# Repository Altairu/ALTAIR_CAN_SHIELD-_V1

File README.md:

# ALTAIR_CAN_SHIELD-_V1
ALTAIR_CAN_SHIELD _V1

注意：ファイルが破損しています．
発注ファイルはCAN_V1_1.zip

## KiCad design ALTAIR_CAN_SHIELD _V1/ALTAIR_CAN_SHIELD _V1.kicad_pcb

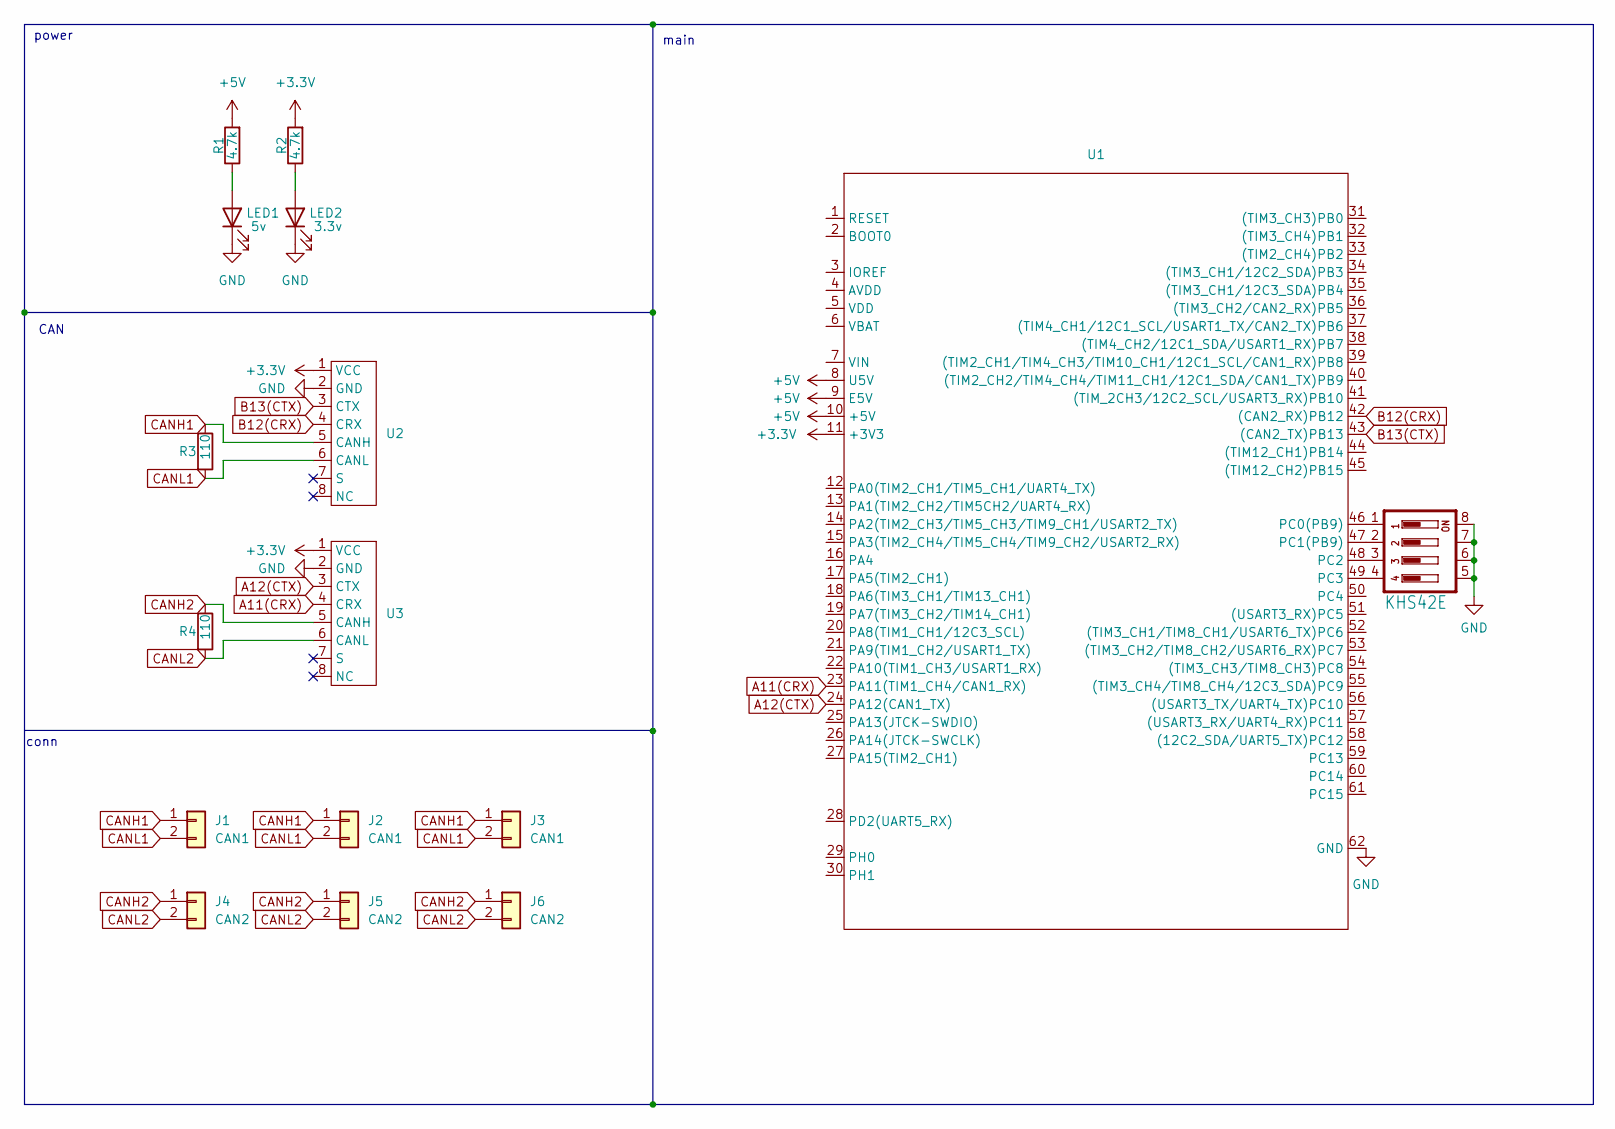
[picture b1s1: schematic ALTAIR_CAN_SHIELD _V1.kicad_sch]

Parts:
J1, J2, J3: CAN1; JST_XA_S02B-XASK-1_1x02_P2.50mm_Horizontal
J4, J5, J6: CAN2; JST_XA_S02B-XASK-1_1x02_P2.50mm_Horizontal
LED1: 5v; LED_D3.0mm
LED2: 3.3v; LED_D3.0mm
R1, R2: 4.7k; R_Axial_DIN0207_L6.3mm_D2.5mm_P10.16mm_Horizontal
R3, R4: 110; R_Axial_DIN0207_L6.3mm_D2.5mm_P10.16mm_Horizontal
S2: KHS42E; SOIC-8_3.9x4.9mm_P1.27mm
U1: STM32F446RE_Nucleo
U2, U3: TJA1051

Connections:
+3.3V: R2.2, U1.11 (+3V3), U2.1 (VCC), U3.1 (VCC)
+5V: R1.2, U1.8 (U5V), U1.9 (E5V), U1.10 (+5V)
A11(CRX): U1.23 (PA11(TIM1_CH4/CAN1_RX)), U3.4 (CRX)
A12(CTX): U1.24 (PA12(CAN1_TX)), U3.3 (CTX)
B12(CRX): U1.42 ((CAN2_RX)PB12), U2.4 (CRX)
B13(CTX): U1.43 ((CAN2_TX)PB13), U2.3 (CTX)
CANH1: J1.1, J2.1, J3.1, R3.1, U2.5 (CANH)
CANH2: J4.1, J5.1, J6.1, R4.1, U3.5 (CANH)
CANL1: J1.2, J2.2, J3.2, R3.2, U2.6 (CANL)
CANL2: J4.2, J5.2, J6.2, R4.2, U3.6 (CANL)
GND: LED1.1 (K), LED2.1 (K), S2.5, S2.6, S2.7, S2.8, U1.62 (GND), U2.2 (GND), U3.2 (GND)
unnamed: LED1.2 (A), R1.1
unnamed: LED2.2 (A), R2.1
unnamed: S2.1, U1.46 (PC0(PB9))
unnamed: S2.2, U1.47 (PC1(PB9))
unnamed: S2.3, U1.48 (PC2)
unnamed: S2.4, U1.49 (PC3)

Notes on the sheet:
CAN
main
power
conn

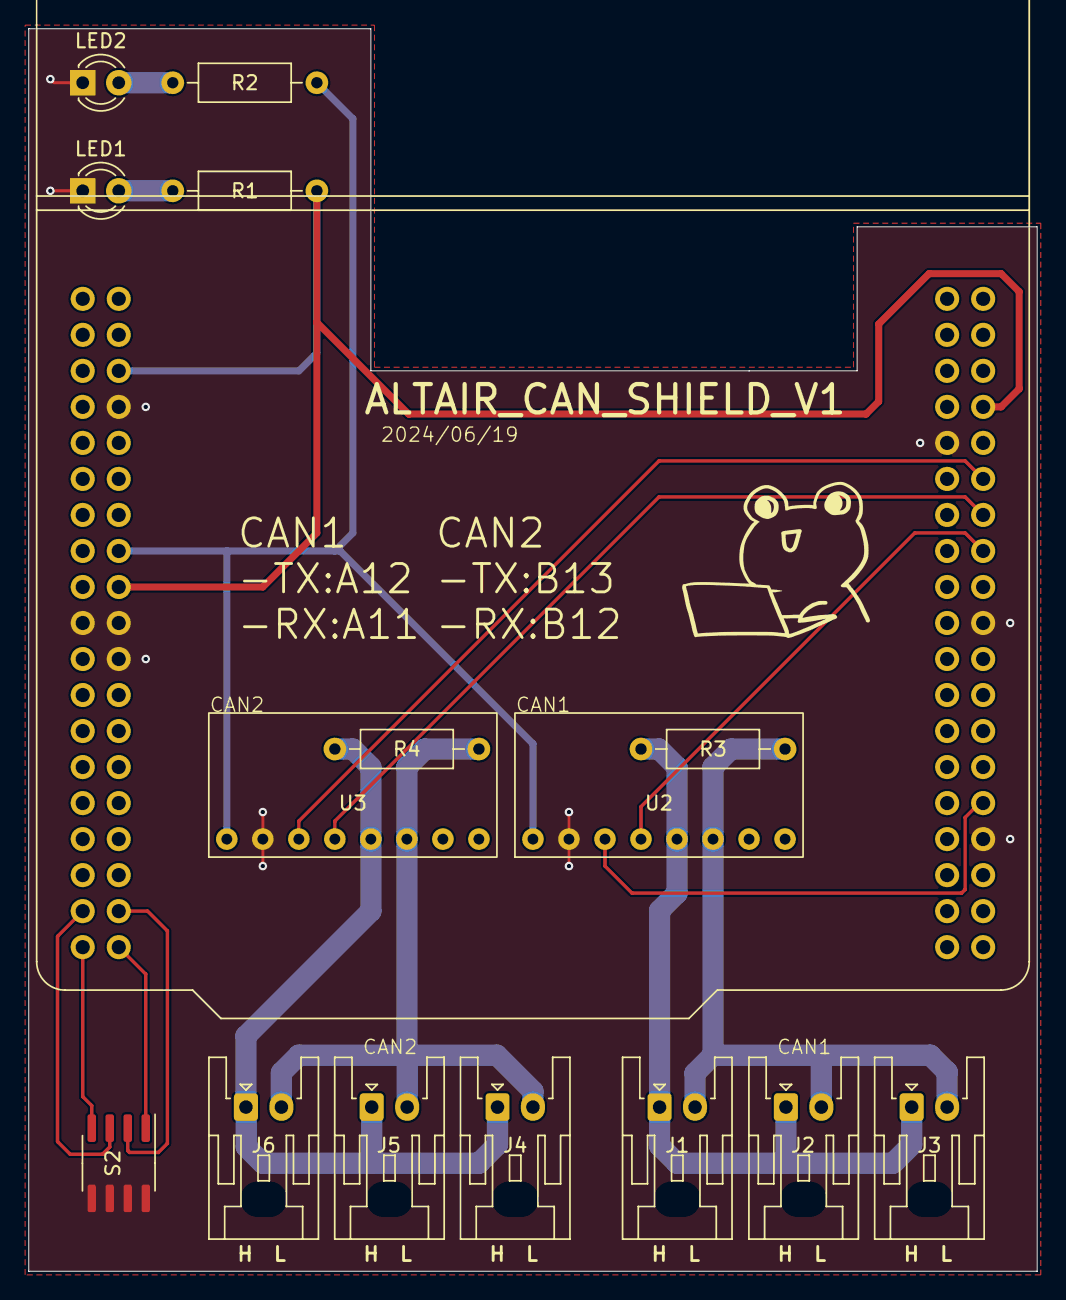
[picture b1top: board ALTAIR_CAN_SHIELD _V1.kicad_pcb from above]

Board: 2 copper layers, 71.1 x 87.6 mm, 16 parts (0 on the bottom side), 17 nets.
